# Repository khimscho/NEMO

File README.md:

# Low-cost Data Logger System

## Purpose

This repository contains the hardware designs, firmware source code, and supporting applications and libraries for a low-cost data logger aimed at the NMEA ([National Marine Electronics Association](https://www.nmea.org)) 0183 and 2000 protocols, as used in many marine electronics systems.  The goal is to provide a minimally-functional system to record the data appearing on NMEA0183 and NMEA2000 busses on board ships, which can be used to provide volunteer depth observations (and many other things) to assist in mapping the oceans.

## Why Have Another Logger?

There is a robust infrastructure of data loggers for both NMEA0183 and NMEA2000 busses, but they are often intended for different purposes (e.g., voyage data recorders, WiFi gateways, etc.), and they are typically order US$250 [2020] or more.  This project came out of efforts within the [Seabed 2030](https://seabed2030.gebco.net) project to map the world ocean completely by 2030, where large-scale mapping is required if the goals of the programme are to be met.  Consequently, while volunteer data is a part of the solution, it has to be something that can be scaled to very large data collections.  Since it has proven hard to sustain open data collection of this type (most of the sustained efforts have been closed, with data only going back to the collectors, and not to open databases), we believe that the only viable financial model for this purpose is to give the hardware away for free, rather than attempting to sell it for profit.  That is, the hardware is free to the data collector, who is asked just to host the hardware on their ship.  Because of this model, we need the hardware to be as low-cost as possible.

This project is therefore aimed at designing as simple, and low-cost, a logger as possible, so that as many as possible can be built and distributed to assist in mapping the oceans.  The target price is order US$30 [2020] for one interface (either NMEA0183 or NMEA2000), or US$40 [2020] for both interfaces.

At the same time, we recognise that getting data from the loggers into the national and international databases can be difficult, and ask a lot of the volunteer data collectors.  The project is therefore also attempting to define a workflow for submission of data to the [International Hydrographic Office](https://iho.int)'s [Data Center for Digital Bathymetry](https://www.ngdc.noaa.gov/iho/), hosted by the [National Centers for Environmental Information](https://www.ngdc.noaa.gov) in Boulder, CO.  The goal is to have a "Trusted Node in a Box", so that anyone wanting to support collection of data of this kind has everything they need to support a very basic data flowpath direct from the loggers through the cloud to DCDB.  (Developers are then free to add on anything else they need.)

## What Does the Logger Do?

The logger's functionality is deliberately constrained.  During normal operations, the logger monitors the NMEA0183 and/or NMEA2000 busses to which it is attached, and records any valid data packet received to local storage.  Timestamps are provided through the elapsed time counter on the microcontroller used, and although a pseudo-time is computed from NMEA2000 data packets if they are available, there is no expectation that timestamps will be assigned until the data is uploaded for processing.

The logger provides an always-on Bluetooth Low Energy service that acts as a software UART.  Client software can connect to this service and pass ASCII commands to the logger to control logging, determine the files that have been logged and their sizes, manage log files, set non-volatile parameters for the system, and so on.  Critically, the BLE service can also be used to start and stop the logger's WiFi service, which is used to give higher-speed transfer of data (although it also responds to all of the same commands).  This avoids having another WiFi network on board the ship if it is not required.

After upload to a mobile collection device (e.g., a cell-phone or tablet), the data is then sent to Amazon Web Services at the first stable communications connection of the mobile device, at which point it is processed, reformatted, packaged, and transmitted to DCDB for archive.

## Concept of Operations

This logger is designed for supported, focussed, data collections.  In this mode, loggers would be provided by an organisation in a specific geographic location to support data collection in a particular area.  The goal here is to provide density of observations in an area, which greatly assists in processing the data, and making useful products.  In addition to providing the loggers (and recruiting the volunteer observers), the organisation would also provide local support personnel to visit the volunteer observers, pick up the collected data (via mobile device), and make sure that the loggers were still collecting data.  Having local support also ensures that there is continued communication with the observers, which is useful in sustaining the community in the long term.

After each visit, all of the data collected (potentially from multiple observers) on the mobile device can be uploaded to any available service that implements the cloud segment of the software suite.  This could be something set up specifically for the organisation using the model provided here, or it could be a third-party that provides an equivalent.

## Licensing and Distribution

In order to provide for the widest possible use (and to avoid excuses ...) the hardware designs, firmware source, and supporting libraries are all released as Open Source under the MIT license.  The cloud segment is released under the MIT License for non-commercial use; for commercial licenses, please contact info@ccom.unh.edu.

## Where to Start

The source for the system is maintained in a [BitBucket repository](https://bitbucket.org/brian_r_calder/sb2030logger), which also includes a Wiki for details of the design and system development.

To build the system, you will need at least:

1. A functional Python interpreter (at least 3.6).

2. A working [Arduino](https://www.arduino.cc) development environment (at least 1.8.12), or equivalent (e.g., [embedXcode](https://embedxcode.weebly.com) 11.8.8).

3. Support for [Espressif](https://www.espressif.com) ESP32 development (with Arduino 1.8.12 this can be installed from the IDE, see [here](https://github.com/espressif/arduino-esp32) for instructions).

4. Support for NMEA2000 handling on ESP32 (you need the [base library](https://github.com/ttlappalainen/NMEA2000) and [ESP-specific](https://github.com/ttlappalainen/NMEA2000_esp32) extensions).

5. Eagle CAD (at least 9.5.2) for the hardware designs.

6. A working C++11 (at least) compiler for the software data simulator.

With these prerequisites, the recommended place to start is with the logger firmware, followed with the data parser Python, which will allow you to demonstrate that your logger is actually logging data.  For benchtop testing, the hardware data simulator can be used (with the development board) to generate simulated data on both NMEA0183 and NMEA2000 for testing logger modifications.  The WiFi Command GUI can be used to interact with a logger once WiFi is enabled, allowing you to transfer files, and decode them.

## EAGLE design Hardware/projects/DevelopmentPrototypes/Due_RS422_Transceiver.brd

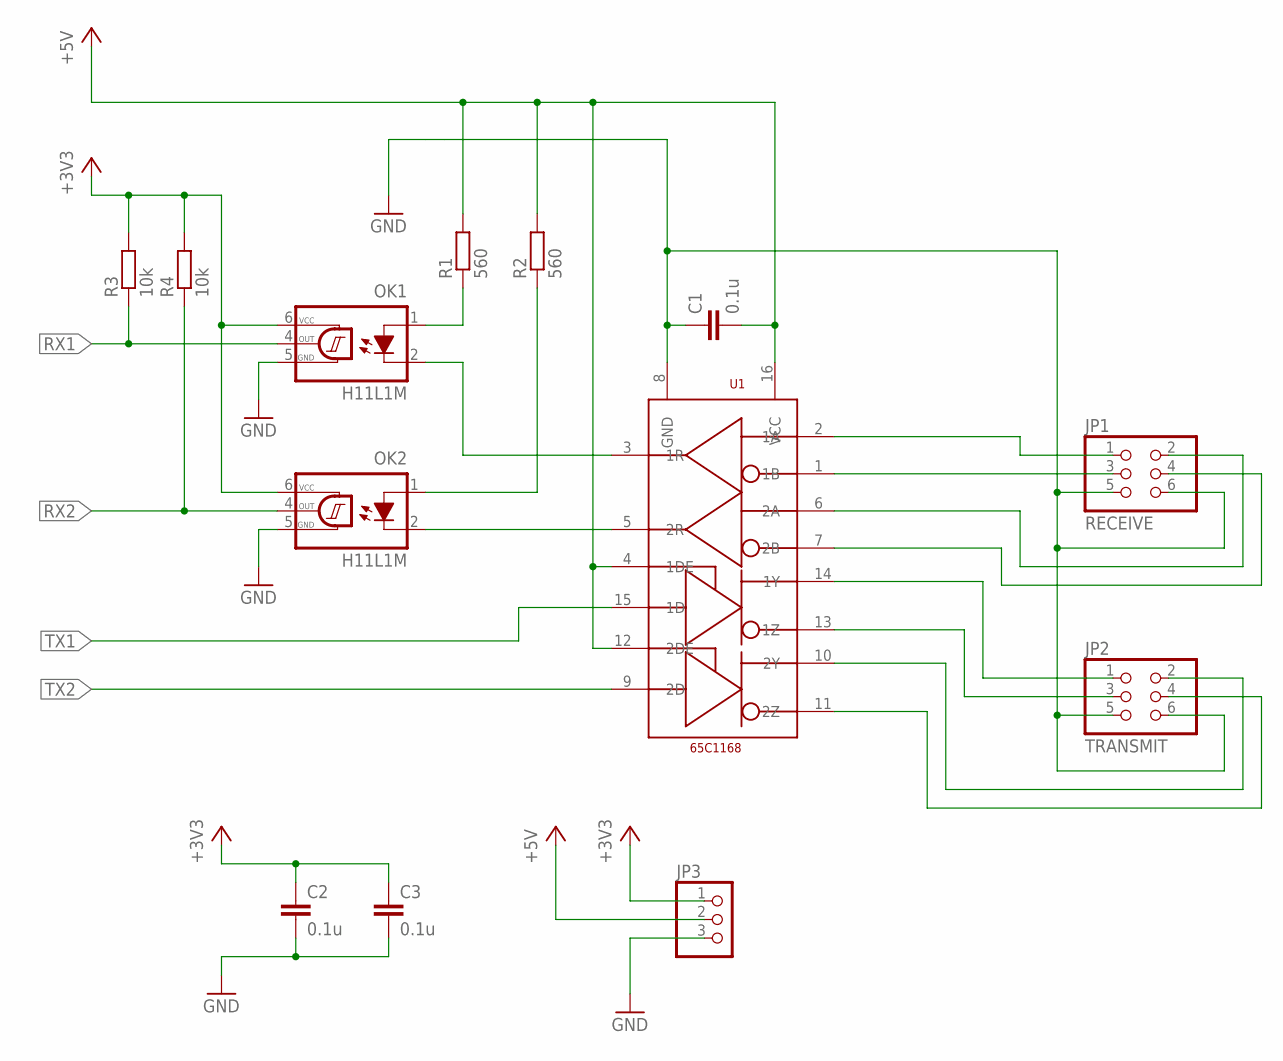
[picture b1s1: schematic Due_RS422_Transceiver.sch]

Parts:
C1, C2, C3: 0.1u; C050-030X075
JP1: RECEIVE; 2X03
JP2: TRANSMIT; 2X03
JP3: PINHD-1X3; 1X03
OK1, OK2: H11L1M; DIL06
R1, R2: 560; 0204/7
R3, R4: 10k; 0204/7
U1: 65C1168; DIP16

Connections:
+3V3: C2.1, C3.1, JP3.1, OK1.6 (VCC), OK2.6 (VCC), R3.2, R4.2
+5V: C1.2, JP3.2, R1.2, R2.2, U1.4 (1DE), U1.12 (2DE), U1.16 (VCC)
GND: C1.1, C2.2, C3.2, JP1.5, JP1.6, JP2.5, JP2.6, JP3.3, OK1.5 (GND), OK2.5 (GND), U1.8 (GND)
unnamed: OK1.2 (C), U1.3 (1R)
unnamed: OK2.2 (C), U1.5 (2R)
unnamed: OK1.1 (A), R1.1
unnamed: OK2.1 (A), R2.1
unnamed: JP1.3, U1.1 (1B)
unnamed: JP1.1, U1.2 (1A)
unnamed: JP1.2, U1.6 (2A)
unnamed: JP1.4, U1.7 (2B)
unnamed: JP2.1, U1.14 (1Y)
unnamed: JP2.3, U1.13 (1Z)
unnamed: JP2.2, U1.10 (2Y)
unnamed: JP2.4, U1.11 (2Z)
RX1: OK1.4 (OUT), R3.1
RX2: OK2.4 (OUT), R4.1
TX1: U1.15 (1D)
TX2: U1.9 (2D)

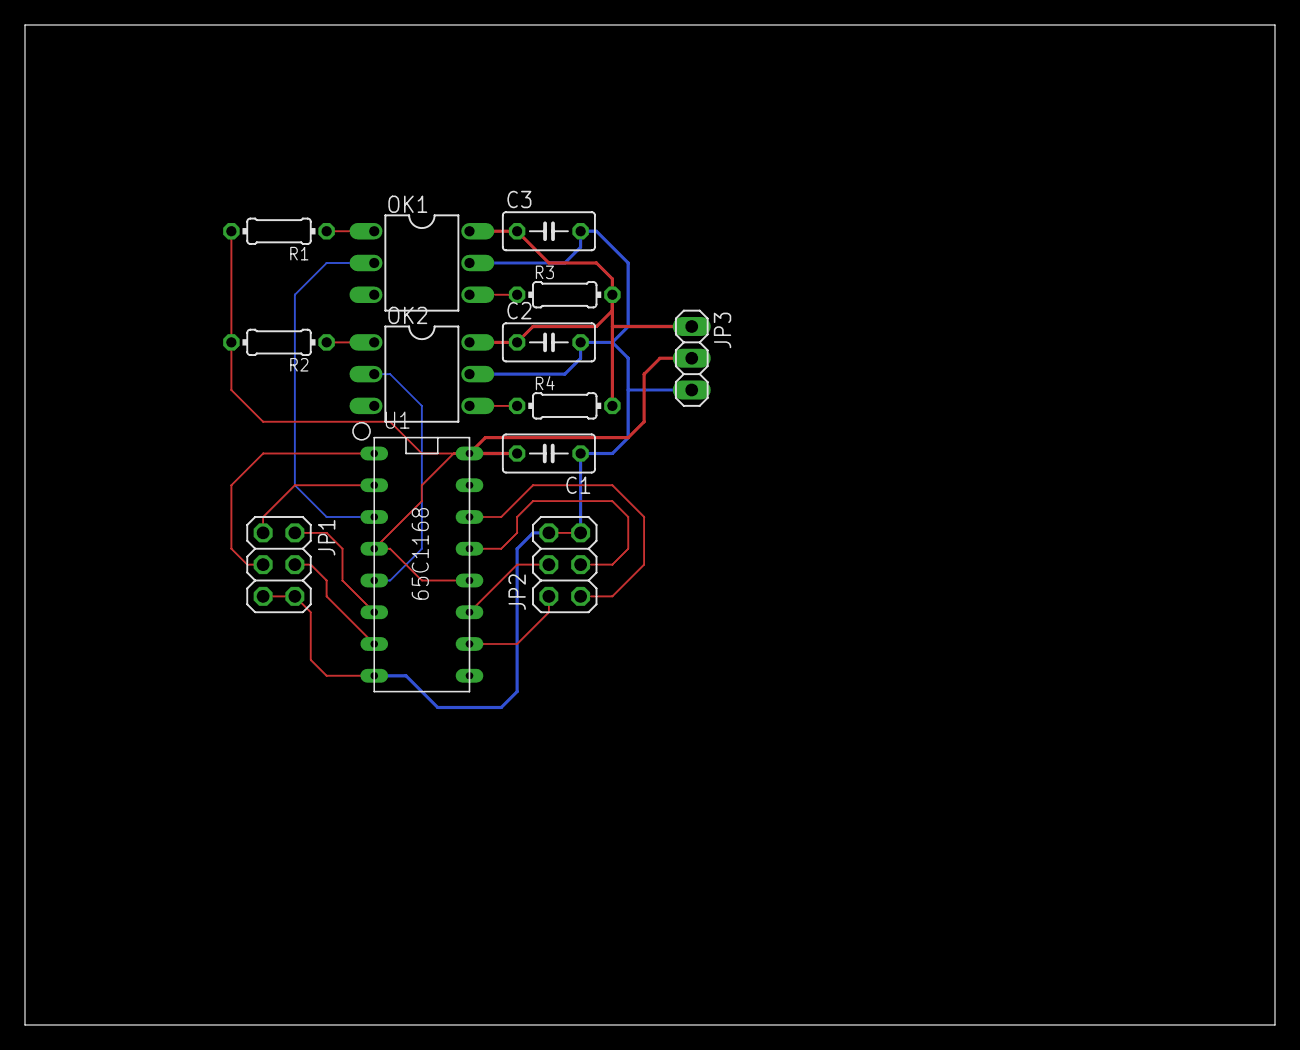
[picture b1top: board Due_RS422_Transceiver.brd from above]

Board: 2 copper layers, 100.0 x 80.0 mm, 13 parts (0 on the bottom side), 17 nets.

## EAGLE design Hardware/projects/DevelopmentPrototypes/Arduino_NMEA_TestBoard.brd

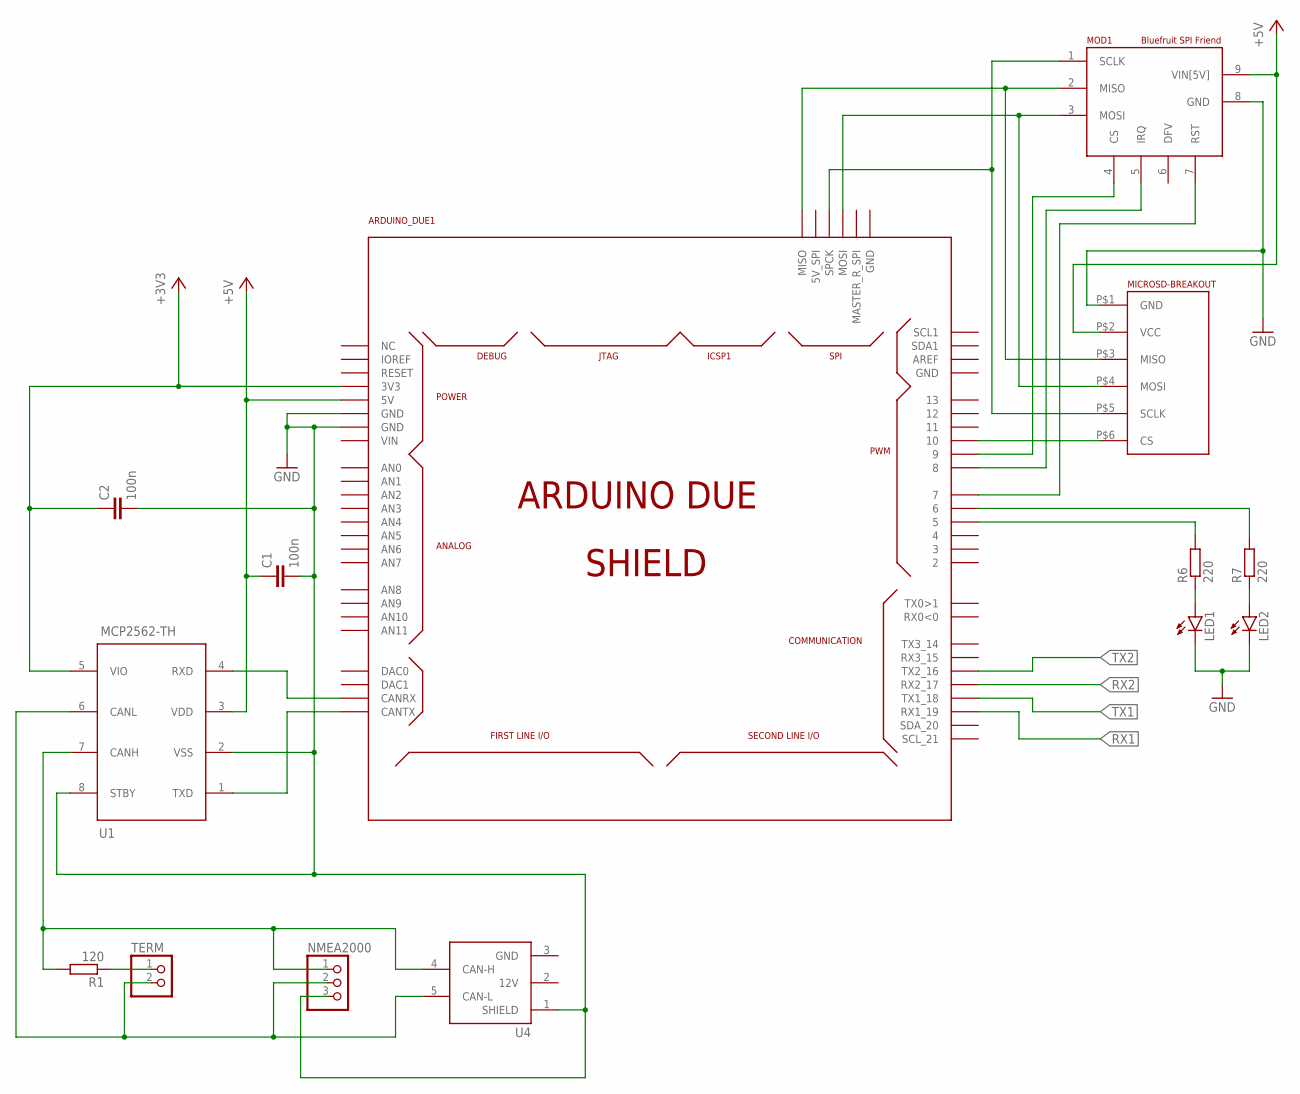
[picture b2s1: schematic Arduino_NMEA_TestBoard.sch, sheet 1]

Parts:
ARDUINO_DUE1: ARDUINO_DUE_SHIELD
C1, C2: 100n; C050-025X075
LED1, LED2: LED5MM
MICROSD-BREAKOUT: MICROSD-BREAKOUT
MOD1: BLUEFRUIT-SPI-FRIEND; BLE_SPIFRIEND
NMEA2000: PINHD-1X3; 1X03
R1: 120; 0207/10
R6, R7: 220; 0207/10
TERM: PINHD-1X2; 1X02
U1: MCP2562-TH; DIP8
U4: NMEA2000-TOPSIDE

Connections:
+3V3: ARDUINO_DUE1.3V3, C2.1, U1.5 (VIO); also elsewhere on the board
+5V: ARDUINO_DUE1.5V0 (5V), C1.1, MICROSD-BREAKOUT.P$2 (VCC), MOD1.9 (VIN[5V]), U1.3 (VDD); also elsewhere on the board
GND: ARDUINO_DUE1.GND, ARDUINO_DUE1.GND_1 (GND), C1.2, C2.2, LED1.K (C), LED2.K (C), MICROSD-BREAKOUT.P$1 (GND), MOD1.8 (GND), NMEA2000.3, U1.2 (VSS), U1.8 (STBY), U4.1 (SHIELD); also elsewhere on the board
unnamed: ARDUINO_DUE1.SPCK, MICROSD-BREAKOUT.P$5 (SCLK), MOD1.1 (SCLK)
unnamed: ARDUINO_DUE1.CANRX, U1.4 (RXD)
unnamed: ARDUINO_DUE1.CANTX, U1.1 (TXD)
unnamed: NMEA2000.2, TERM.2, U1.6 (CANL), U4.5 (CAN-L)
unnamed: NMEA2000.1, R1.2, U1.7 (CANH), U4.4 (CAN-H)
unnamed: ARDUINO_DUE1.MISO, MICROSD-BREAKOUT.P$3 (MISO), MOD1.2 (MISO)
unnamed: ARDUINO_DUE1.MOSI, MICROSD-BREAKOUT.P$4 (MOSI), MOD1.3 (MOSI)
unnamed: R1.1, TERM.1
unnamed: ARDUINO_DUE1.10, MICROSD-BREAKOUT.P$6 (CS)
unnamed: ARDUINO_DUE1.9, MOD1.4 (CS)
unnamed: ARDUINO_DUE1.8, MOD1.5 (IRQ)
unnamed: ARDUINO_DUE1.7, MOD1.7 (RST)
unnamed: ARDUINO_DUE1.5, R6.2
unnamed: ARDUINO_DUE1.6, R7.2
unnamed: LED1.A, R6.1
unnamed: LED2.A, R7.1
RX1: ARDUINO_DUE1.19 (RX1_19); also elsewhere on the board
RX2: ARDUINO_DUE1.17 (RX2_17); also elsewhere on the board
TX1: ARDUINO_DUE1.18 (TX1_18); also elsewhere on the board
TX2: ARDUINO_DUE1.16 (TX2_16); also elsewhere on the board

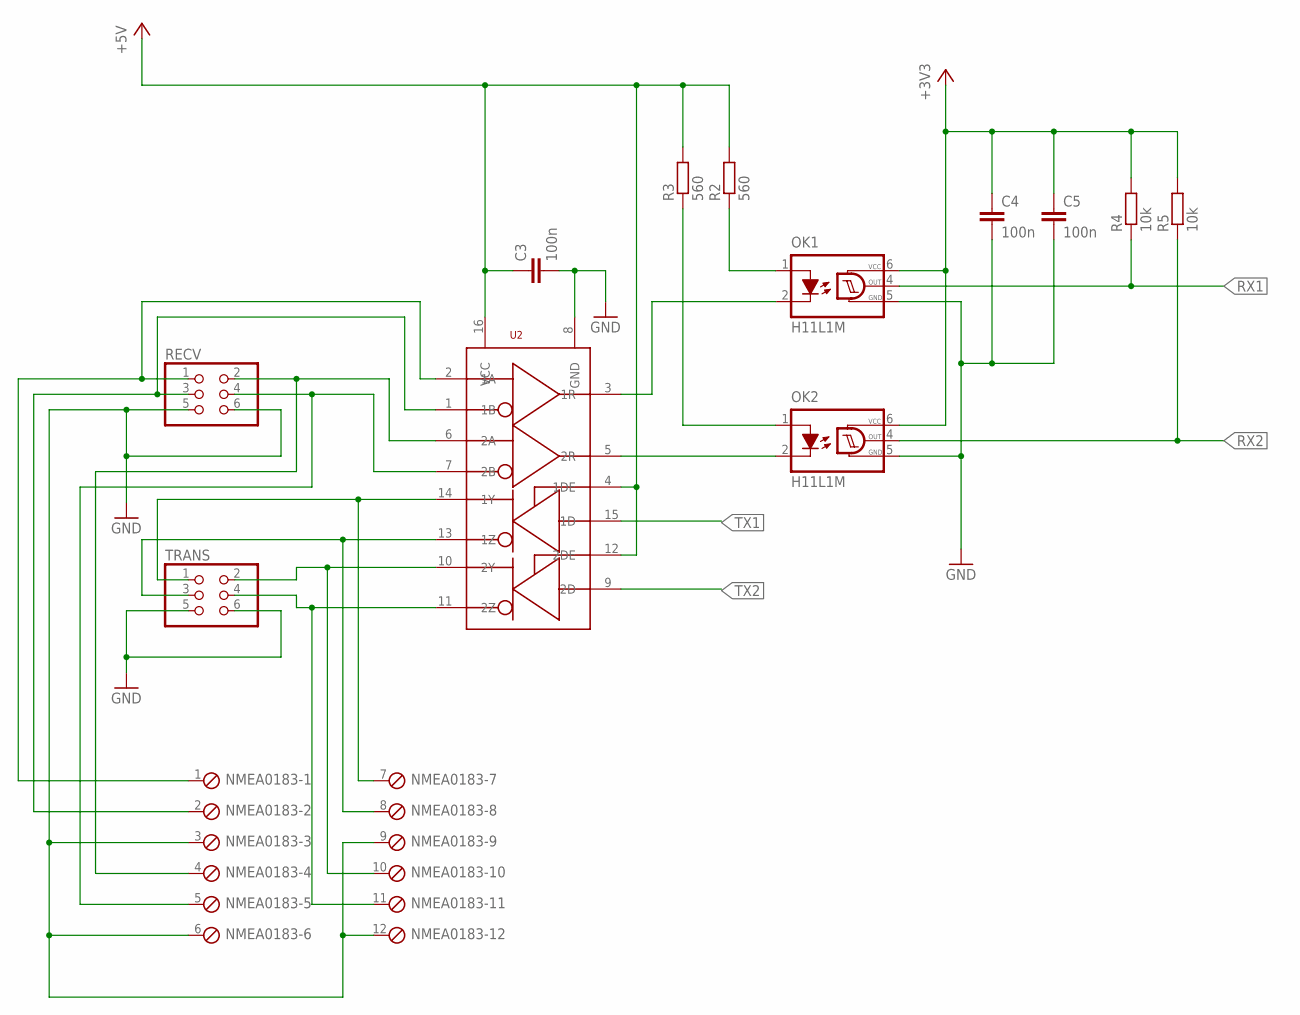
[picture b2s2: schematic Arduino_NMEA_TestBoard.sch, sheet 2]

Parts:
C3, C4, C5: 100n; C050-025X075
NMEA0183: MPT12; 12POL254
OK1, OK2: H11L1M; DIL06
R2, R3: 560; 0207/10
R4, R5: 10k; 0207/10
RECV: PINHD-2X3; 2X03
TRANS: PINHD-2X3; 2X03
U2: SN65C1168; DIP16

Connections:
+3V3: C4.1, C5.1, OK1.6 (VCC), OK2.6 (VCC), R4.2, R5.2; also elsewhere on the board
+5V: C3.1, R2.2, R3.2, U2.4 (1DE), U2.12 (2DE), U2.16 (VCC); also elsewhere on the board
GND: C3.2, C4.2, C5.2, NMEA0183.3, NMEA0183.6, NMEA0183.9, NMEA0183.12, OK1.5 (GND), OK2.5 (GND), RECV.5, RECV.6, TRANS.5, TRANS.6, U2.8 (GND); also elsewhere on the board
unnamed: OK2.2 (C), U2.5 (2R)
unnamed: OK1.2 (C), U2.3 (1R)
unnamed: OK1.1 (A), R2.1
unnamed: OK2.1 (A), R3.1
unnamed: NMEA0183.1, RECV.1, U2.2 (1A)
unnamed: NMEA0183.2, RECV.3, U2.1 (1B)
unnamed: NMEA0183.4, RECV.2, U2.6 (2A)
unnamed: NMEA0183.5, RECV.4, U2.7 (2B)
unnamed: NMEA0183.8, TRANS.3, U2.13 (1Z)
unnamed: NMEA0183.10, TRANS.2, U2.10 (2Y)
unnamed: NMEA0183.7, TRANS.1, U2.14 (1Y)
unnamed: NMEA0183.11, TRANS.4, U2.11 (2Z)
RX1: OK1.4 (OUT), R4.1; also elsewhere on the board
RX2: OK2.4 (OUT), R5.1; also elsewhere on the board
TX1: U2.15 (1D); also elsewhere on the board
TX2: U2.9 (2D); also elsewhere on the board

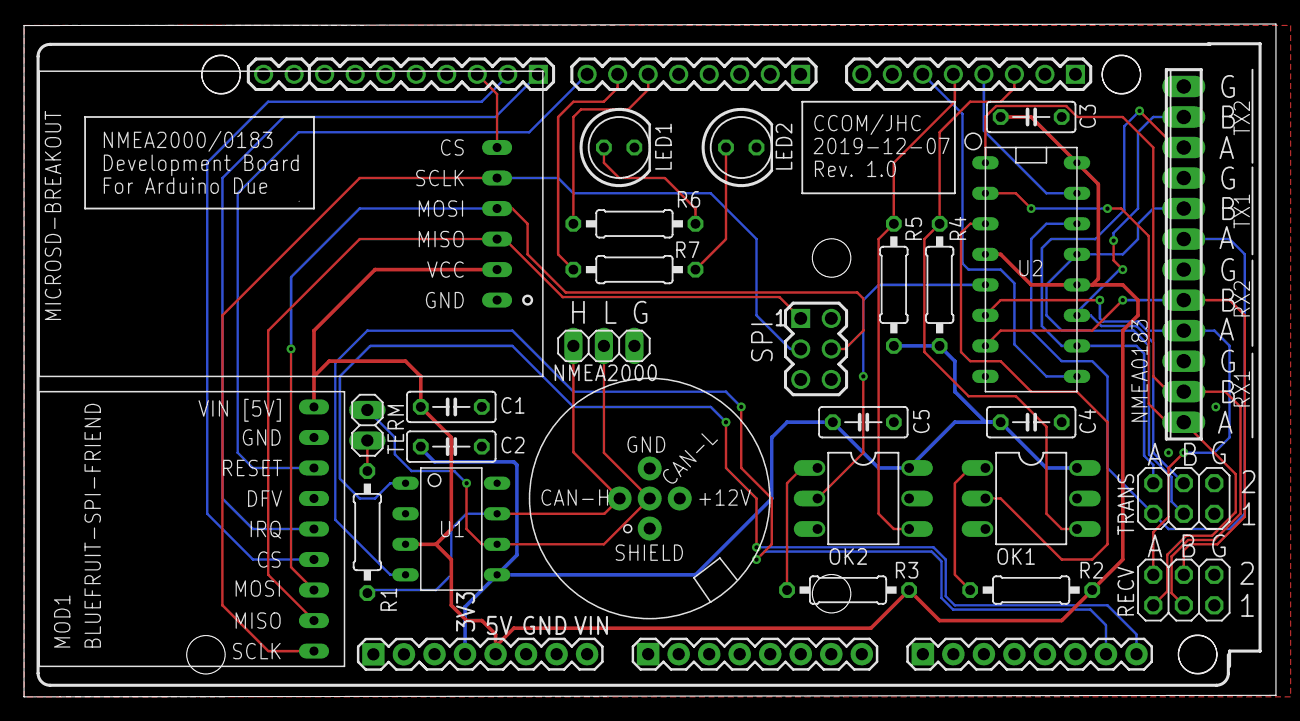
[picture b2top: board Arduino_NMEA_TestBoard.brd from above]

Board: 2 copper layers, 104.2 x 56.0 mm, 27 parts (0 on the bottom side), 35 nets.

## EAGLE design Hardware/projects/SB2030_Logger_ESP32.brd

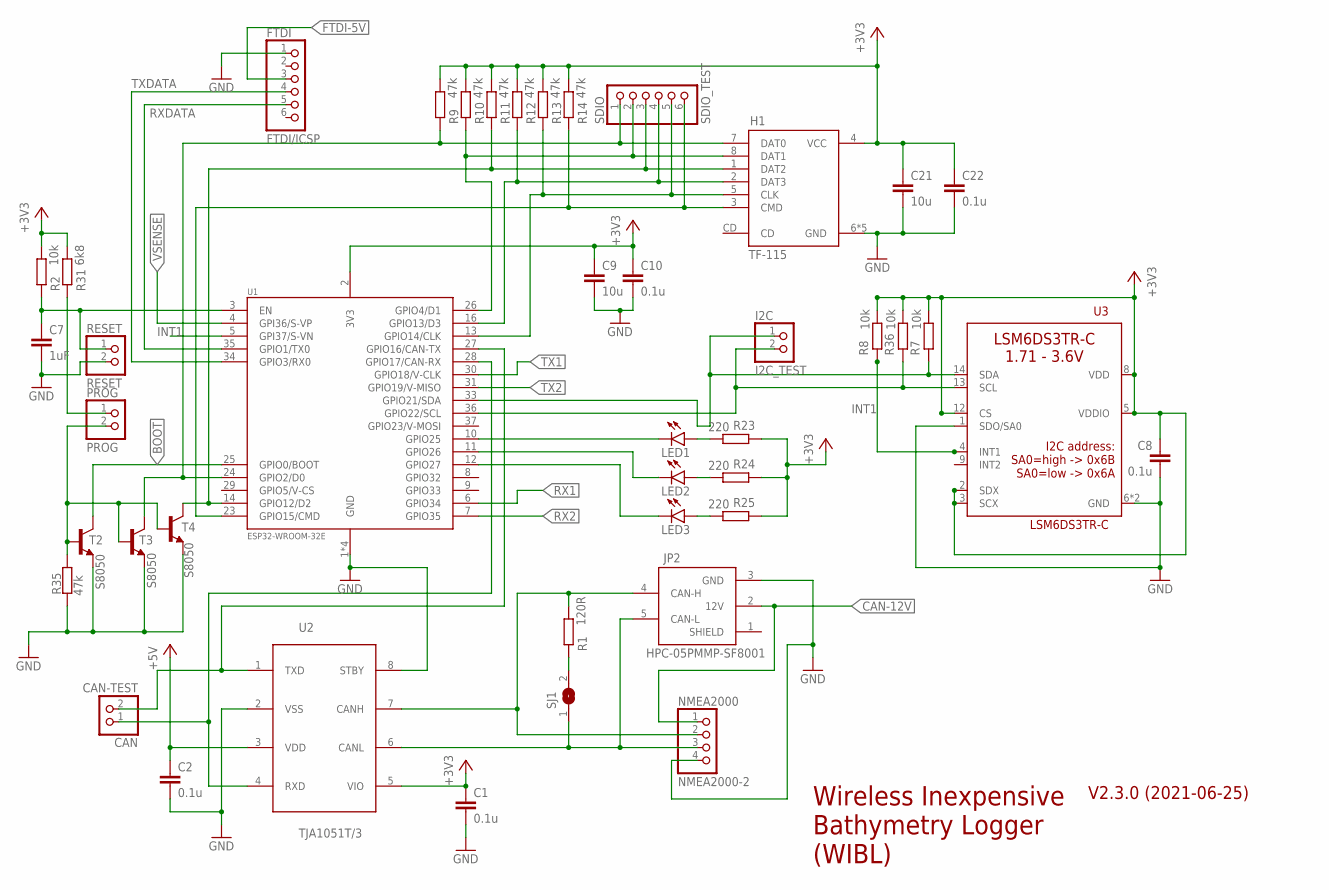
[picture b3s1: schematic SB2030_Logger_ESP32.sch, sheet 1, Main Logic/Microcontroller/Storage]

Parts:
C1, C2, C8, C10, C22: 0.1u; C0805
C7: 1uF; C0805
C9, C21: 10u; C0805
CAN: CAN-TEST; 1X02
FTDI: FTDI/ICSP; 1X06
H1: TF-115; XUNPU-MICROSD-SOCKET
I2C: I2C_TEST; 1X02
JP2: HPC-05PMMP-SF8001; NMEA2000
LED1, LED2, LED3: LEDCHIP-LED0603; CHIP-LED0603
NMEA2000: NMEA2000-2; 1X04
PROG: PROG; 1X02
R1: 120R; R0805
R2, R7, R8, R36: 10k; R0805
R9, R10, R11, R12, R13, R14, R35: 47k; R0805
R23, R24, R25: 220; R0805
R31: 6k8; R0805
RESET: RESET; 1X02
SDIO: SDIO_TEST; 1X06
SJ1: SJ
T2, T3, T4: S8050; SOT23
U1: ESP32-WROOM-32E; ESPS32-WROOM-32E
U2: TJA1051T/3; SOIC8
U3: LSM6DS3TR-C; LGA-14-2.5X3MM

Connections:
+3V3: C1.1, C8.1, C9.1, C10.1, C21.1, C22.1, H1.4 (VCC), R2.2, R7.2, R8.2, R9.2, R10.2, R11.2, R12.2, R13.2, R14.2, R23.1, R24.1, R25.1, R31.2, R36.2, U1.2 (3V3), U2.5 (VIO), U3.2 (SDX), U3.3 (SCX), U3.5 (VDDIO), U3.8 (VDD), U3.12 (CS); also elsewhere on the board
+5V: C2.1, U2.3 (VDD); also elsewhere on the board
BOOT: T2.3 (C), U1.25 (GPIO0/BOOT); also elsewhere on the board
CAN-12V: JP2.2 (12V), NMEA2000.1; also elsewhere on the board
FTDI-5V: FTDI.3; also elsewhere on the board
GND: C1.2, C2.2, C7.2, C8.2, C9.2, C10.2, C21.2, C22.2, FTDI.1, H1.6 (GND), H1.GND1 (GND), H1.GND2 (GND), H1.GND3 (GND), H1.GND4 (GND), JP2.3 (GND), NMEA2000.4, R35.1, RESET.2, T2.2 (E), T3.2 (E), T4.2 (E), U1.1 (GND), U1.15 (GND), U1.38 (GND), U1.THERM (GND), U2.2 (VSS), U2.8 (STBY), U3.1 (SDO/SA0), U3.6 (GND), U3.7 (GND); also elsewhere on the board
INT1: R8.1, U1.5 (GPI37/S-VN), U3.4 (INT1)
unnamed: JP2.4 (CAN-H), NMEA2000.2, R1.2, U2.7 (CANH)
unnamed: JP2.5 (CAN-L), NMEA2000.3, SJ1.1, U2.6 (CANL)
unnamed: R1.1, SJ1.2
unnamed: C7.1, R2.1, RESET.1, U1.3 (EN)
unnamed: CAN.2, U1.27 (GPIO16/CAN-TX), U2.1 (TXD)
unnamed: CAN.1, U1.28 (GPIO17/CAN-RX), U2.4 (RXD)
unnamed: H1.1 (DAT2), R11.1, SDIO.3, T4.3 (C), U1.14 (GPIO12/D2)
unnamed: H1.8 (DAT1), R10.1, SDIO.2, U1.26 (GPIO4/D1)
unnamed: H1.7 (DAT0), R9.1, SDIO.1, T3.3 (C), U1.24 (GPIO2/D0)
unnamed: H1.2 (DAT3), R12.1, SDIO.4, U1.16 (GPIO13/D3)
unnamed: H1.5 (CLK), R13.1, SDIO.5, U1.13 (GPIO14/CLK)
unnamed: H1.3 (CMD), R14.1, SDIO.6, U1.23 (GPIO15/CMD)
unnamed: LED1.C, U1.10 (GPIO25)
unnamed: LED2.C, U1.11 (GPIO26)
unnamed: PROG.2, R35.2, T2.1 (B), T3.1 (B), T4.1 (B)
unnamed: LED3.C, U1.12 (GPIO27)
unnamed: LED1.A, R23.2
unnamed: LED2.A, R24.2
unnamed: PROG.1, R31.1
unnamed: LED3.A, R25.2
RX1: U1.6 (GPIO34); also elsewhere on the board
RX2: U1.7 (GPIO35); also elsewhere on the board
RXDATA: FTDI.5, U1.35 (GPIO1/TX0)
SCL: I2C.1, R7.1, U1.33 (GPIO21/SDA), U3.14 (SDA)
SDA: I2C.2, R36.1, U1.36 (GPIO22/SCL), U3.13 (SCL)
TX1: U1.30 (GPIO18/V-CLK); also elsewhere on the board
TX2: U1.31 (GPIO19/V-MISO); also elsewhere on the board
TXDATA: FTDI.4, U1.34 (GPIO3/RX0)
VSENSE: U1.4 (GPI36/S-VP); also elsewhere on the board

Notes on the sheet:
Wireless Inexpensive Bathymetry Logger (WIBL)
V2.3.0 (2021-06-25)

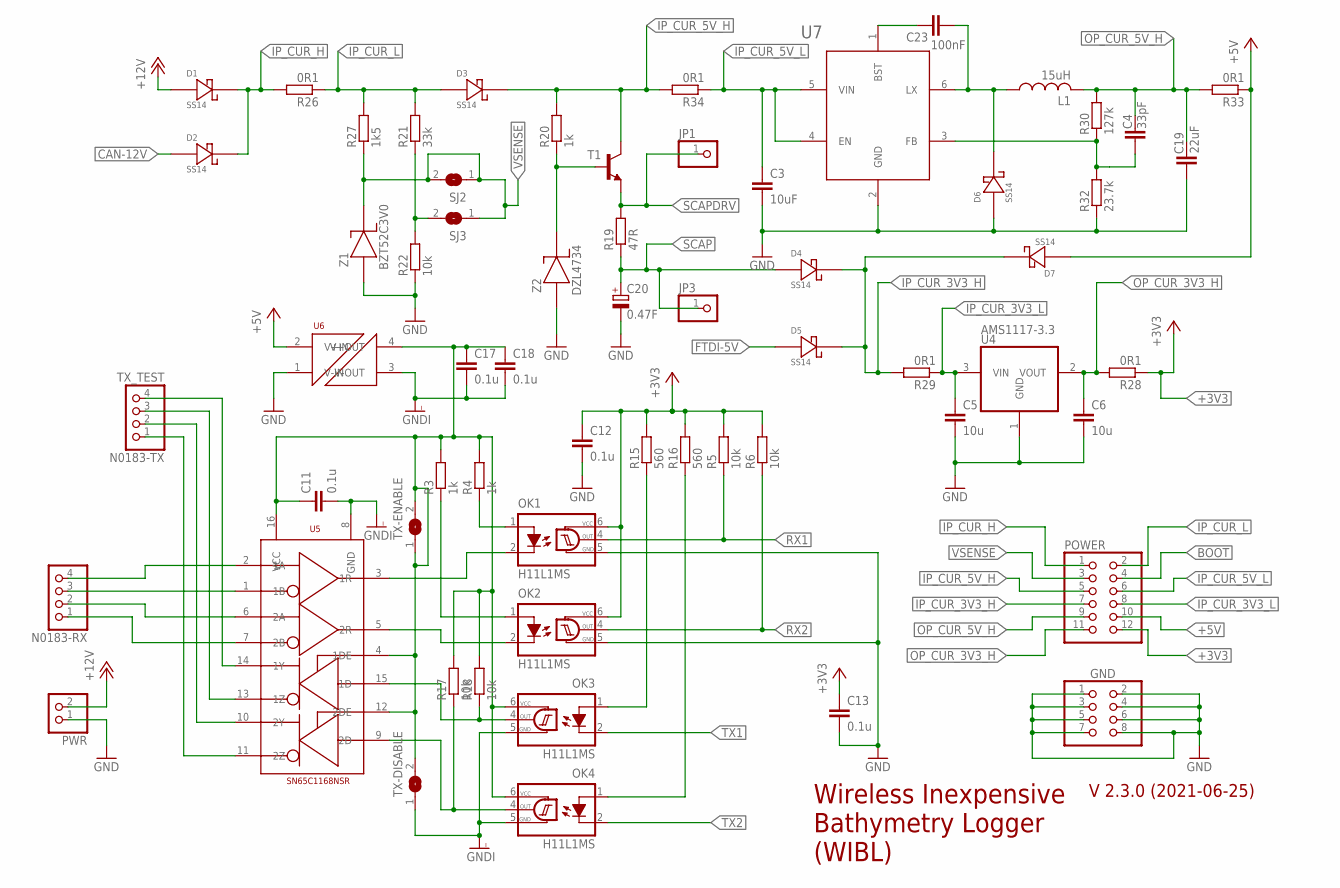
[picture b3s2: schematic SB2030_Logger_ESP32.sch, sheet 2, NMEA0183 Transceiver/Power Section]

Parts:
C3: 10uF; C1206
C4: 33pF; C0603
C5, C6: 10u; C0805
C11, C12, C13, C17, C18: 0.1u; C0805
C19: 22uF; C0603
C20: 0.47F; P128-50
C23: 100nF; C0402
D1, D2, D3, D4, D5, D6, D7: SS14; DO-214AC
GND: PINHD-2X4; 2X04
JP1, JP3: PINHD-1X1; 1X01
L1: 15uH; MWSA0603S
N0183-RX: PINHD-1X4; 1X04
N0183-TX: TX_TEST; 1X04
OK1, OK2, OK3, OK4: H11L1MS; DIL6-SMD
POWER: PINHD-2X6; 2X06
PWR: PINHD-1X2; 1X02
R3, R4, R20: 1k; R0805
R5, R6, R17, R18, R22: 10k; R0805
R15, R16: 560; R0805
R19: 47R; R0805
R21: 33k; R0805
R26, R28, R29, R33, R34: 0R1; R0603
R27: 1k5; R0805
R30: 127k; R0603
R32: 23.7k; R0603
SJ2, SJ3: SJ
T1: BC817-16-NPN-SOT23-BEC; SOT23-BEC
TX-DISABLE: SJ
TX-ENABLE: SJ
U4: AMS1117-3.3; SOT223
U5: SN65C1168NSR; SOIC16
U6: RFM-0505S
U7: BL9352A; SOT-23-6L
Z1: BZT52C3V0; SOD123
Z2: DZL4734; SOD-123FL

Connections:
+3V3: C12.1, C13.1, OK1.6 (VCC), OK2.6 (VCC), POWER.12, R5.2, R6.2, R15.2, R16.2, R28.1; also elsewhere on the board
+5V: D7.A, POWER.10, R33.1, U6.2 (V+IN); also elsewhere on the board
+12V: D1.A, PWR.2
BOOT: POWER.4; also elsewhere on the board
CAN-12V: D2.A; also elsewhere on the board
FTDI-5V: D5.A; also elsewhere on the board
GND: C3.2, C5.2, C6.2, C12.2, C13.2, C19.1, C20.-, D6.A, GND.1, GND.2, GND.3, GND.4, GND.5, GND.6, GND.7, GND.8, OK1.5 (GND), OK2.5 (GND), PWR.1, R22.1, R32.1, U4.1 (GND), U6.1 (V-IN), U7.2 (GND), Z1.1 (A), Z2.A; also elsewhere on the board
GNDI: C11.2, C17.2, C18.2, OK3.5 (GND), OK4.5 (GND), TX-DISABLE.1, U5.8 (GND), U6.3 (V-OUT)
IP_CUR_3V3_H: D4.K, D5.K, D7.K, POWER.7, R29.2
IP_CUR_3V3_L: C5.1, POWER.8, R29.1, U4.3 (VIN)
IP_CUR_5V_H: D3.K, POWER.5, R20.2, R34.2, T1.C
IP_CUR_5V_L: C3.1, POWER.6, R34.1, U7.4 (EN), U7.5 (VIN)
IP_CUR_H: D1.K, D2.K, POWER.1, R26.2
IP_CUR_L: D3.A, POWER.2, R21.2, R26.1, R27.2
unnamed: OK1.2 (C), U5.3 (1R)
unnamed: OK2.2 (C), U5.5 (2R)
unnamed: OK1.1 (A), R4.1
unnamed: OK2.1 (A), R3.1
unnamed: N0183-RX.4, U5.2 (1A)
unnamed: N0183-RX.3, U5.1 (1B)
unnamed: N0183-RX.2, U5.6 (2A)
unnamed: N0183-RX.1, U5.7 (2B)
unnamed: C11.1, C17.1, C18.1, OK3.6 (VCC), OK4.6 (VCC), R3.2, R4.2, R17.2, R18.2, TX-DISABLE.2, TX-ENABLE.1, TX-ENABLE.2, U5.4 (1DE), U5.12 (2DE), U5.16 (VCC), U6.4 (V+OUT)
unnamed: N0183-TX.4, U5.14 (1Y)
unnamed: N0183-TX.3, U5.13 (1Z)
unnamed: N0183-TX.2, U5.10 (2Y)
unnamed: N0183-TX.1, U5.11 (2Z)
unnamed: OK3.1 (A), R15.1
unnamed: OK4.1 (A), R16.1
unnamed: OK3.4 (OUT), R18.1, U5.15 (1D)
unnamed: OK4.4 (OUT), R17.1, U5.9 (2D)
unnamed: R20.1, T1.B, Z2.K
unnamed: C23.P$1 (1), U7.1 (BST)
unnamed: C23.P$2 (2), D6.K, L1.P$1 (1), U7.6 (LX)
unnamed: R21.1, R22.2, SJ3.2
unnamed: C4.1, R30.1, R32.2, U7.3 (FB)
OP_CUR_3V3_H: C6.1, POWER.11, R28.2, U4.2 (VOUT)
OP_CUR_5V_H: C4.2, C19.2, L1.P$2 (2), POWER.9, R30.2, R33.2
RX1: OK1.4 (OUT), R5.1; also elsewhere on the board
RX2: OK2.4 (OUT), R6.1; also elsewhere on the board
SCAP: C20.+, D4.A, JP3.1, R19.1
SCAPDRV: JP1.1, R19.2, T1.E
TX1: OK3.2 (C); also elsewhere on the board
TX2: OK4.2 (C); also elsewhere on the board
VSENSE: POWER.3, R27.1, SJ2.1, SJ2.2, SJ3.1, Z1.2 (K); also elsewhere on the board

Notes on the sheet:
Wireless Inexpensive Bathymetry Logger (WIBL)
V 2.3.0 (2021-06-25)

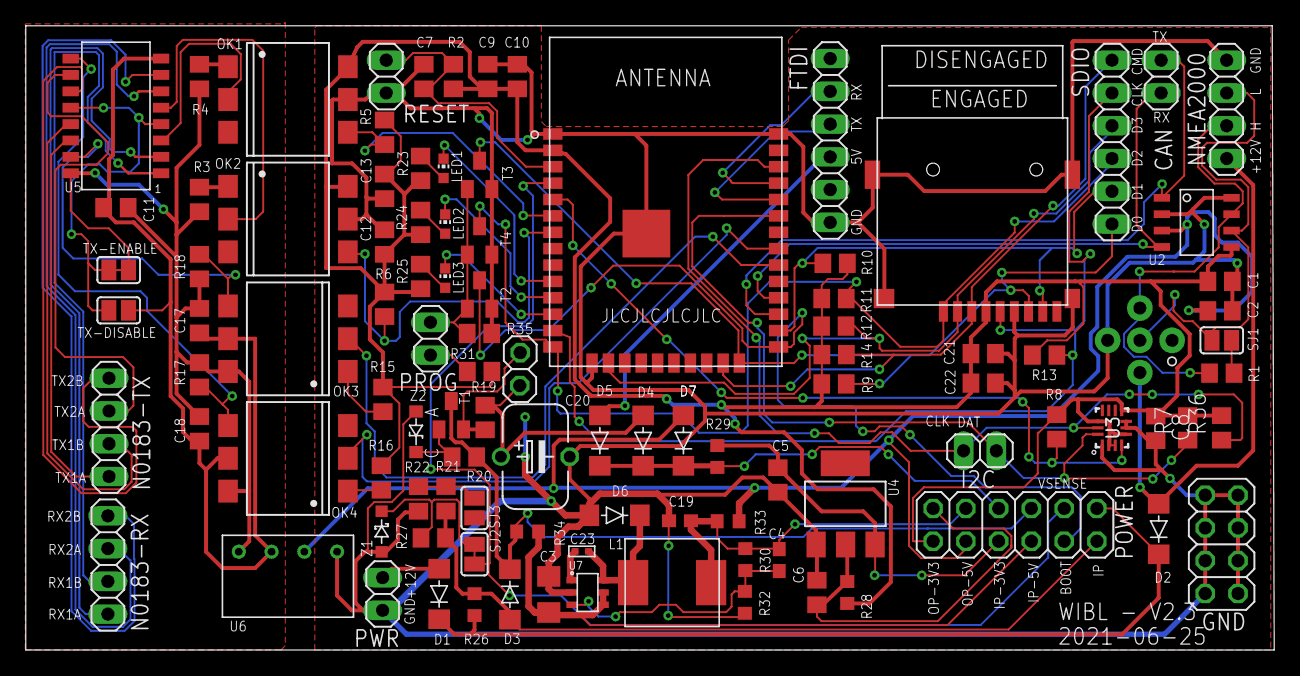
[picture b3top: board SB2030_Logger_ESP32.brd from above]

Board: 2 copper layers, 96.8 x 48.4 mm, 105 parts (0 on the bottom side), 70 nets.

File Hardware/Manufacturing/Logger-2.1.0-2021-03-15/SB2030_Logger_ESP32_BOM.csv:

Qty,Designator,Footprint,Comment,LCSC Part #,Description
1,DZL4734,SOD-123FL,5.6V Zener,C362311,"Zener Diode, 1W"
1,LED1,CHIP-LED0603,Yellow,C72038,Yellow LED
1,LED2,CHIP-LED0603,Green,C72043,Green LED
1,LED3,CHIP-LED0603,Blue,C72041,Blue LED
12,"C1, C2, C7, C8, C10, C11, C12, C13, C15, C17, C18, C19",C0805,0.1uF,C696366,"CAPACITOR, European symbol"
8,"R2, R5, R6, R7, R8, R17, R18, R22",R0805,10k,C17414,"RESISTOR, European symbol"
1,C16,C0805,10nF,C1710,"CAPACITOR, European symbol"
5,"C3, C4, C5, C6, C9",C0805,10uF,C15850,"CAPACITOR, European symbol"
1,R1,R0805,120R,C17437,"RESISTOR, European symbol"
5,"R26, R27, R28, R29, R30",R0805,1R,C25271,"RESISTOR, European symbol"
3,"R3, R4, R20",R0805,1k,C17513,"RESISTOR, European symbol"
3,"R23, R24, R25",R0805,220R,C17557,"RESISTOR, European symbol"
1,C14,C0805,2.2nF,C28260,"CAPACITOR, European symbol"
1,R21,R0805,33k,C17633,"RESISTOR, European symbol"
1,R19,R0805,47R,C17714,"RESISTOR, European symbol"
6,"R9, R10, R11, R12, R13, R14",R0805,47k,C17713,"RESISTOR, European symbol"
2,"R15, R16",R0805,560R,C28636,"RESISTOR, European symbol"
1,R31,R0805,6k8,C17772,"RESISTOR, European symbol"
1,U4,SOT223,3.3V LDO,C6186,AMS1117-3.3 800mA and 1A Low Dropout (LDO) Positive Regulator
1,U3,SOT223,5.0V LDO,C6187,AMS1117-5.0 800mA and 1A Low Dropout (LDO) Positive Regulator
1,U1,MODULE_ESP-WROOM-32,ESP-WROOM-32,C701341,ESP32-WROOM-32E module
4,"OK1, OK2, OK3, OK4",DIL6-SMD,H11L1MS,C255762,6-Pin DIP Optocoupler
1,U2,SOIC8,TJA1051T/3 CAN transceiver,C38695,CAN bus transceiver
1,U$1,XUNPU-MICROSD-SOCKET,MICRO-SD Holder,C266620,"Micro SD Card Holder, push-push"
1,IC1,QFN50P400X400X95-25T265X275N,MPU6050 6-DoF,C24112,Triple Axis 6-DoF Accelerometer/Gyro
4,"T1, T2, T3, T4",SOT23,S8050,C2146,NPN TRANSISTOR
5,"D1, D2, D3, D4, D5",SOD-123_MINI-SMA,SS14,C2480,Shottky Diode

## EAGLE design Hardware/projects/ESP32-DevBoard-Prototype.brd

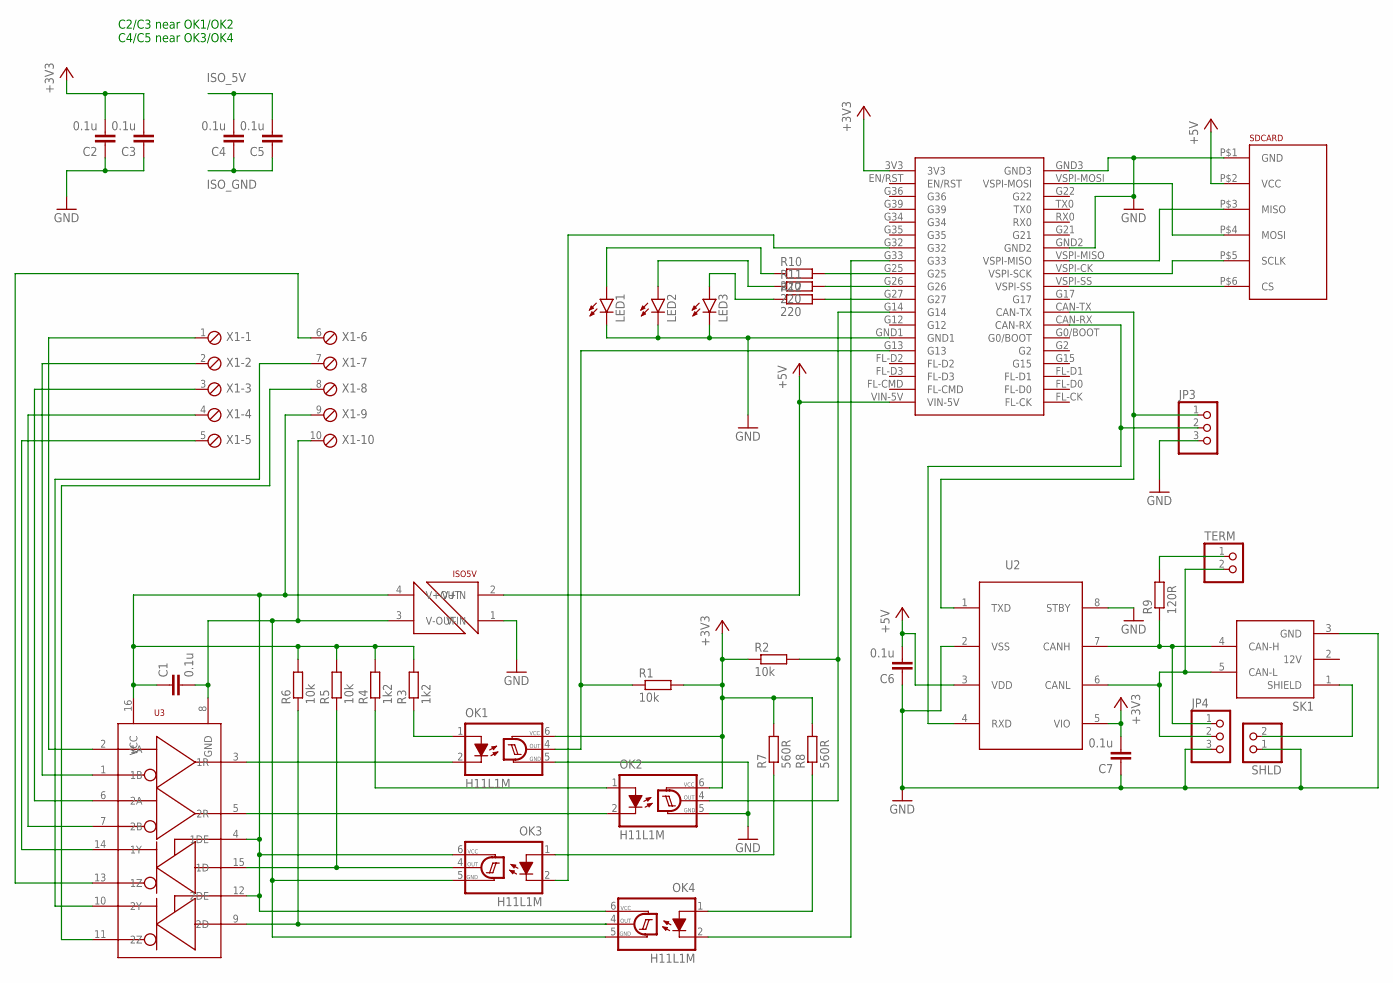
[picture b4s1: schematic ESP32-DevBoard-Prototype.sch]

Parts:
C1, C2, C3, C4, C5, C6, C7: 0.1u; C050-025X075
ISO5V: RFM-0505S
JP3, JP4: PINHD-1X3; 1X03
LED1, LED2, LED3: LED5MM
OK1, OK2, OK3, OK4: H11L1M; DIL06
R1, R2, R5, R6: 10k; 0207/10
R3, R4: 1k2; 0207/10
R7, R8: 560R; 0207/10
R9: 120R; 0207/10
R10, R11, R12: 220; 0207/10
SDCARD: MICROSD-BREAKOUT
SHLD: PINHD-1X2; 1X02
SK1: NMEA2000-TOPSIDE
TERM: PINHD-1X2; 1X02
U1: ESP32-DEVBOARD
U2: MCP2562-TH; DIP8
U3: SN65C1168; DIP16
X1: MPT10; 10POL254

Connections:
+3V3: C2.2, C3.2, C7.2, OK1.6 (VCC), OK2.6 (VCC), R1.2, R2.1, R7.2, R8.2, U1.3V3, U2.5 (VIO)
+5V: C6.2, ISO5V.2 (V+IN), SDCARD.P$2 (VCC), U1.VIN-5V, U2.3 (VDD)
GND: C2.1, C3.1, C6.1, C7.1, ISO5V.1 (V-IN), JP3.3, JP4.3, LED1.K (C), LED2.K (C), LED3.K (C), OK1.5 (GND), OK2.5 (GND), SDCARD.P$1 (GND), SHLD.1, SK1.3 (GND), U1.GND1, U1.GND2, U1.GND3, U2.2 (VSS), U2.8 (STBY)
ISO_5V: C1.1, C4.2, C5.2, ISO5V.4 (V+OUT), OK3.6 (VCC), OK4.6 (VCC), R3.2, R4.2, R5.2, R6.2, U3.4 (1DE), U3.12 (2DE), U3.16 (VCC), X1.9
ISO_GND: C1.2, C4.1, C5.1, ISO5V.3 (V-OUT), OK3.5 (GND), OK4.5 (GND), U3.8 (GND), X1.10
unnamed: JP3.1, U1.CAN-TX, U2.1 (TXD)
unnamed: SDCARD.P$4 (MOSI), U1.VSPI-MOSI
unnamed: OK3.1 (A), R7.1
unnamed: OK1.2 (C), U3.3 (1R)
unnamed: OK2.2 (C), U3.5 (2R)
unnamed: OK3.4 (OUT), R5.1, U3.15 (1D)
unnamed: OK4.4 (OUT), R6.1, U3.9 (2D)
unnamed: OK1.4 (OUT), R1.1, U1.G13
unnamed: OK2.4 (OUT), R2.2, U1.G14
unnamed: OK1.1 (A), R3.1
unnamed: OK2.1 (A), R4.1
unnamed: OK4.1 (A), R8.1
unnamed: SDCARD.P$3 (MISO), U1.VSPI-MISO
unnamed: OK3.2 (C), U1.G32
unnamed: OK4.2 (C), U1.G33
unnamed: SDCARD.P$5 (SCLK), U1.VSPI-CK (VSPI-SCK)
unnamed: SDCARD.P$6 (CS), U1.VSPI-SS
unnamed: JP3.2, U1.CAN-RX, U2.4 (RXD)
unnamed: JP4.1, R9.1, SK1.4 (CAN-H), U2.7 (CANH)
unnamed: JP4.2, SK1.5 (CAN-L), TERM.2, U2.6 (CANL)
unnamed: R9.2, TERM.1
unnamed: U3.2 (1A), X1.1
unnamed: SHLD.2, SK1.1 (SHIELD)
unnamed: U3.1 (1B), X1.2
unnamed: U3.6 (2A), X1.3
unnamed: U3.7 (2B), X1.4
unnamed: U3.14 (1Y), X1.5
unnamed: U3.13 (1Z), X1.6
unnamed: U3.10 (2Y), X1.7
unnamed: R10.2, U1.G25
unnamed: U3.11 (2Z), X1.8
unnamed: LED3.A, R12.1
unnamed: LED2.A, R11.1
unnamed: LED1.A, R10.1
unnamed: R11.2, U1.G26
unnamed: R12.2, U1.G27

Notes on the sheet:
C2/C3 near OK1/OK2 C4/C5 near OK3/OK4

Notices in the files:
Hardware/projects/SB2030_Logger_ESP32.brd:
(c) 2021 Center for Coastal and Ocean Mapping
